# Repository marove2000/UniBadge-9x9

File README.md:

# UniBadge 9x9
A simple badge PCP with 9x9 LEDs. Create symbols, figures, pixel art by just soldering LEDs to the spots you want. No programming needed.

## Bill of Material
| Designator | Package            | Quantity | Designation                    |
| ---------- | ------------------ | -------- | ------------------------------ |
| BT1        | 2-Pin connector    | 1        | Battery-Holder (2xAAA)         |
| C1, C2     | 100nF              | 2        |                                |
| C3         | 0805 SMD capacitor | 1        | variable (see capaictor table) |
| D1-D81     | 0805 SMD LED       | 1-81     | LED red, green, orange, ...    |
| Q1-Q9      | Mosfet             | 9        | 2N7002                         |
| R1, R2     | 0805 SMD resistor  | 2        | 100k                           |
| R3-R11     | 0805 SMD resistor  | 9        | variable (see resistor table)  |
| SW1        | SMD switch         | 1        |                                |
| U1         | SOIC-8 NE555       | 1        |                                |
| U2         | SOP-16 CD4017      | 1        |                                |

### Capacitor-Table for C3
The frequency is determined by the value of C3. Always on: The frequency is so fast, it looks like all (soldered) LEDs are always on.

| Frequency          | Capacitor Value (C3)       |
| ------------------ | -------------------------- |
| slow (~5Hz)        | 1µF                        |
| faster (~50Hz)     | 10nF                       |
| always on (~110Hz) | 4700pF / 4,7nF             |

### Resistor-Table for R3-R11
Resistor values depend on the number of soldered LEDs per row (refer to the table below). Note that you can only choose one LED color per row.

| Number of LEDs | Resistor value for red LEDs | Resistor value for green LEDs (bright!) |
| -------------- | --------------------------- | --------------------------------------- |
| 1              | 56 Ohm                      | 110 Ohm                                 |
| 2              | 27 Ohm                      | 56 Ohm                                  |
| 3              | 18 Ohm                      | 36 Ohm                                  |
| 4              | 15 Ohm                      | 30 Ohm                                  |
| 5              | 11 Ohm                      | 22 Ohm                                  |
| 6              | 9,1 Ohm                     | 18 Ohm                                  |
| 7              | 8,2 Ohm                     | 16 Ohm                                  |
| 8              | 6,8 Ohm                     | 13 Ohm                                  |
| 9              | 6,2 Ohm                     | 12 Ohm                                  |

## Manual
TBD

## Some creations
Some $humans did an amazing job. Here are some awesome examples:

## Copyright and Authorship
- PCB layout: [CC-BY-SA 4.0](https://creativecommons.org/licenses/by-sa/4.0/) - [Thomas Schmid and Timo Schindler](https://www.binary-kitchen.de)
- Manual (TeX): [LPPL](https://www.latex-project.org/lppl.txt) - [Marei Peischl](https://peitex.de)
- Manual (pdf): [CC-BY-SA 4.0](https://creativecommons.org/licenses/by-sa/4.0/) - [Binary Kitchen e.V.](https://www.binary-kitchen.de)

## Acknowledgments
A big thank you goes to Thomas Schmid, Clemens Grünewald and Sandra Schweighart for all the help!

The calculation of the frequency done with https://ohmslawcalculator.com/555-astable-calculator

## Misc: Logo to PCB
The Logos to the PCB are created with an Inkscape plugin

- download and install https://github.com/badgeek/svg2shenzhen
- Inkscape: Extensions -> svg2shenzhen -> Prepare Document
- Choose Layer where to place the logo
- Rename: remove "disabled" from layer-name
- Place logo
- Extensions -> svg2shenshen -> Export Kicad (Kicad-module)
- Copy .kicad_mod in .pretty-folder
- Place as part

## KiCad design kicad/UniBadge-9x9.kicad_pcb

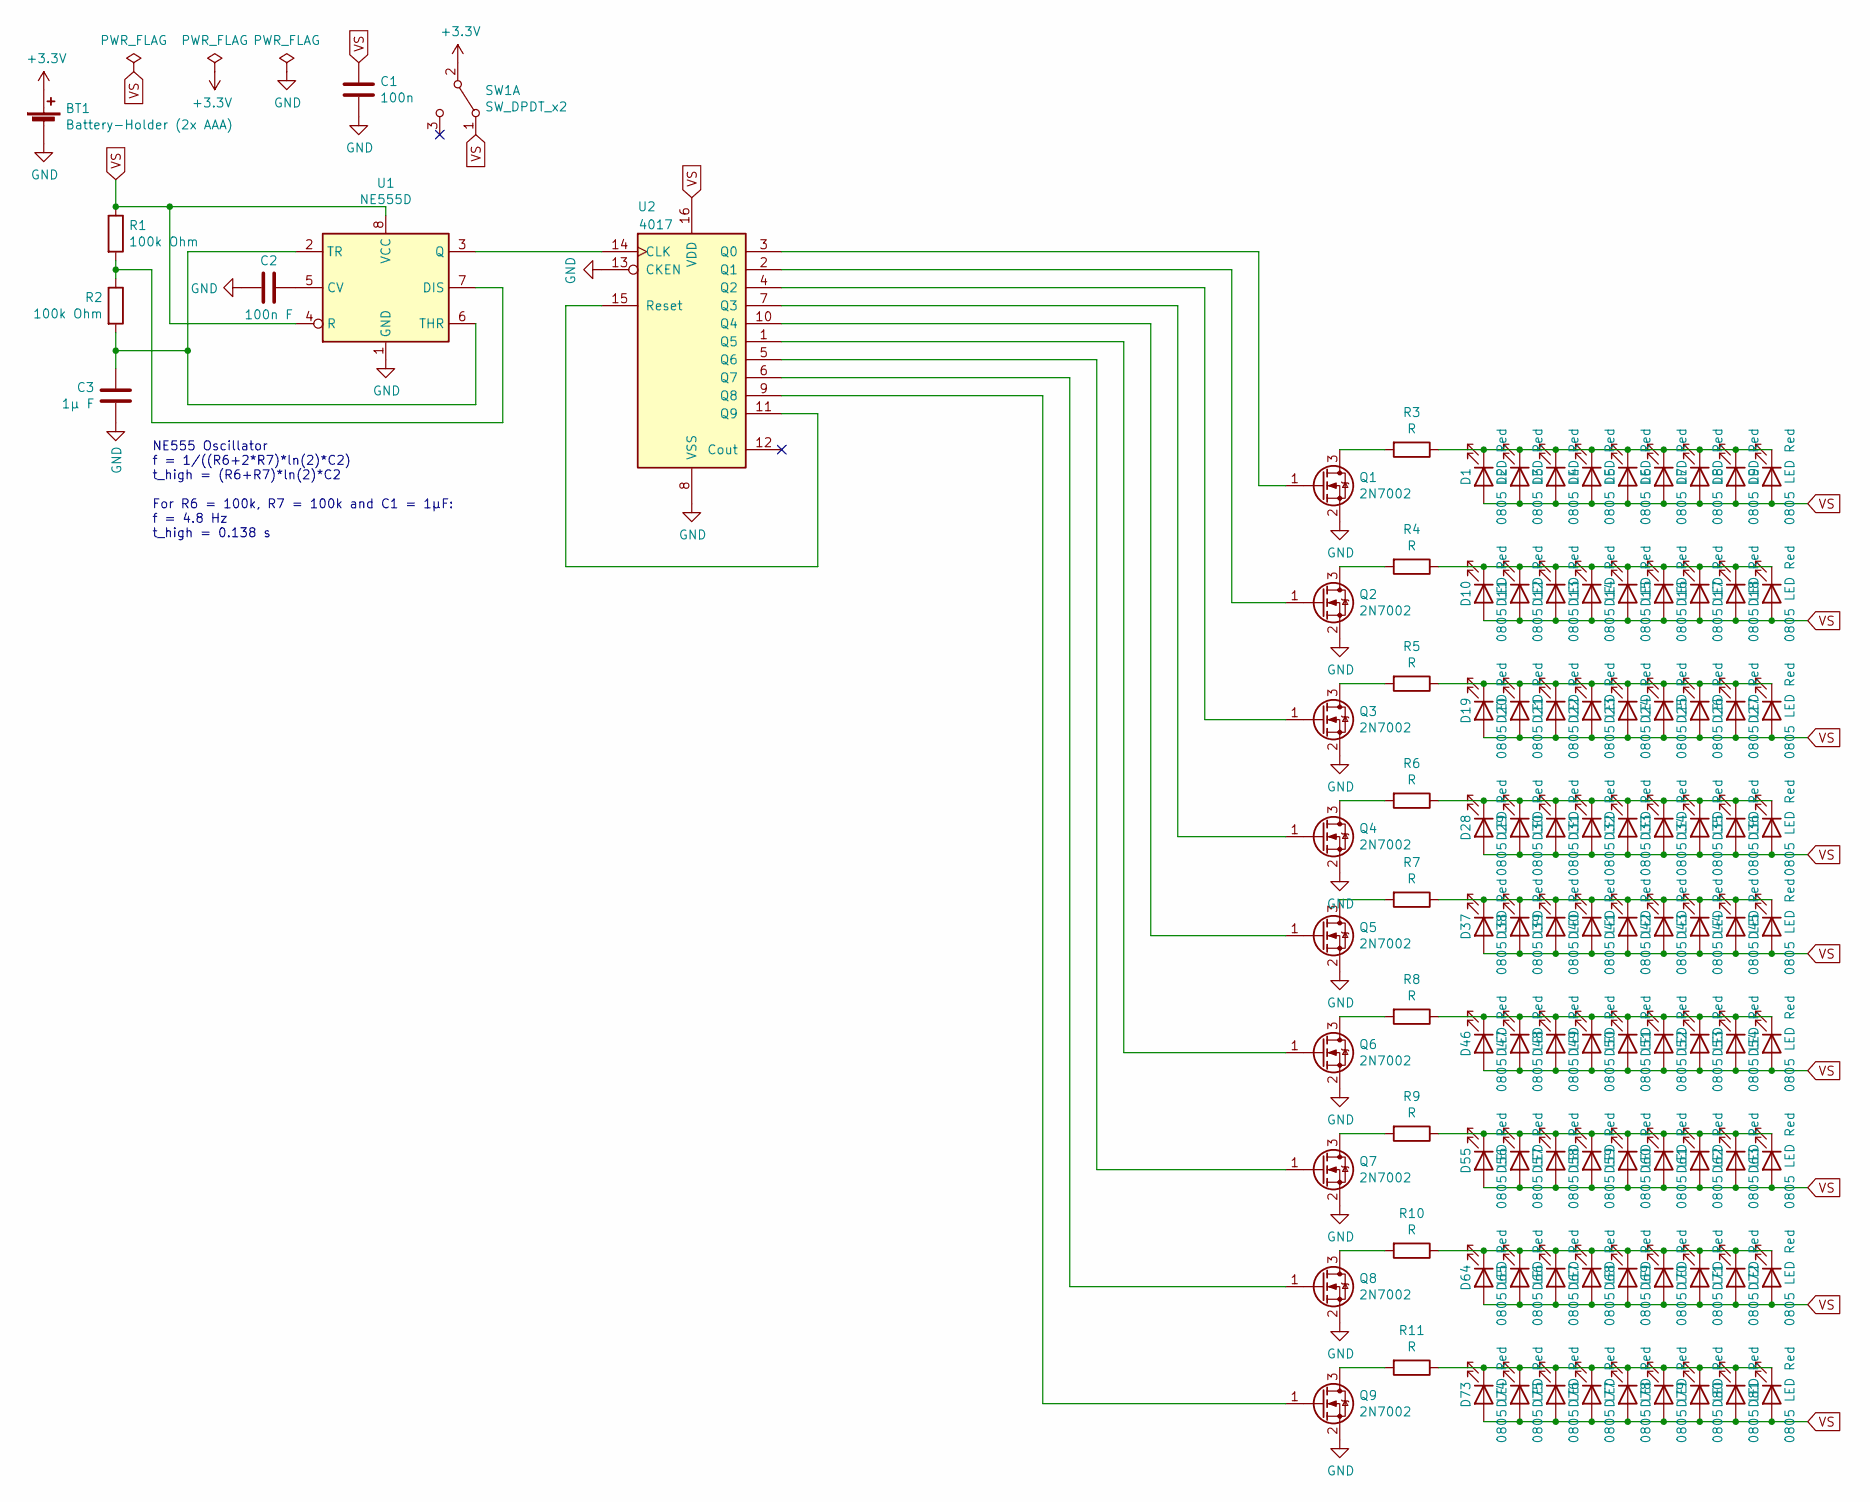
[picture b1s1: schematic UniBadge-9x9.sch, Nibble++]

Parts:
BT1: Battery-Holder (2x AAA); PinHeader_1x02_P2.54mm_Vertical
C1: 100n; C_0805_2012Metric_Pad1.15x1.40mm_HandSolder
C2: 100n F; C_0805_2012Metric_Pad1.15x1.40mm_HandSolder
C3: 1µ F; C_0805_2012Metric_Pad1.15x1.40mm_HandSolder
D1, D2, D3, D4, D5, D6, D7, D8, D9, D10, D11, D12, D13, D14, D15, D16, D17, D18, D19, D20, D21, D22, D23, D24, D25, D26, D27, D28, D29, D30, D31, D32, D33, D34, D35, D36, D37, D38, D39, D40, D41, D42, D43, D44, D45, D46, D47, D48, D49, D50, D51, D52, D53, D54, D55, D56, D57, D58, D59, D60, D61, D62, D63, D64, D65, D66, D67, D68, D69, D70, D71, D72, D73, D74, D75, D76, D77, D78, D79, D80, D81: 0805 LED Red; LED_0805_2012Metric_Pad1.15x1.40mm_HandSolder
Q1, Q2, Q3, Q4, Q5, Q6, Q7, Q8, Q9: 2N7002; SOT-23
R1, R2: 100k Ohm; R_0805_2012Metric_Pad1.15x1.40mm_HandSolder
R3, R4, R5, R6, R7, R8, R9, R10, R11: R; R_0805_2012Metric_Pad1.15x1.40mm_HandSolder
SW1: SW_DPDT_x2; smd_switch_slide
U1: NE555D; SOIC-8_3.9x4.9mm_P1.27mm
U2: 4017; SOP-16_4.4x10.4mm_P1.27mm_simple_drawing

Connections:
+3V3: BT1.1 (+), SW1.2 (B)
GND: BT1.2 (-), C1.1, C2.2, C3.1, Q1.2 (S), Q2.2 (S), Q3.2 (S), Q4.2 (S), Q5.2 (S), Q6.2 (S), Q7.2 (S), Q8.2 (S), Q9.2 (S), U1.1 (GND), U2.8 (VSS), U2.13 (CKEN)
unnamed: C2.1, U1.5 (CV)
unnamed: C3.2, R2.2, U1.2 (TR), U1.6 (THR)
unnamed: D1.1 (K), D2.1 (K), D3.1 (K), D4.1 (K), D5.1 (K), D6.1 (K), D7.1 (K), D8.1 (K), D9.1 (K), R3.1
unnamed: D10.1 (K), D11.1 (K), D12.1 (K), D13.1 (K), D14.1 (K), D15.1 (K), D16.1 (K), D17.1 (K), D18.1 (K), R4.1
unnamed: D19.1 (K), D20.1 (K), D21.1 (K), D22.1 (K), D23.1 (K), D24.1 (K), D25.1 (K), D26.1 (K), D27.1 (K), R5.1
unnamed: D28.1 (K), D29.1 (K), D30.1 (K), D31.1 (K), D32.1 (K), D33.1 (K), D34.1 (K), D35.1 (K), D36.1 (K), R6.1
unnamed: D37.1 (K), D38.1 (K), D39.1 (K), D40.1 (K), D41.1 (K), D42.1 (K), D43.1 (K), D44.1 (K), D45.1 (K), R7.1
unnamed: D46.1 (K), D47.1 (K), D48.1 (K), D49.1 (K), D50.1 (K), D51.1 (K), D52.1 (K), D53.1 (K), D54.1 (K), R8.1
unnamed: D55.1 (K), D56.1 (K), D57.1 (K), D58.1 (K), D59.1 (K), D60.1 (K), D61.1 (K), D62.1 (K), D63.1 (K), R9.1
unnamed: D64.1 (K), D65.1 (K), D66.1 (K), D67.1 (K), D68.1 (K), D69.1 (K), D70.1 (K), D71.1 (K), D72.1 (K), R10.1
unnamed: D73.1 (K), D74.1 (K), D75.1 (K), D76.1 (K), D77.1 (K), D78.1 (K), D79.1 (K), D80.1 (K), D81.1 (K), R11.1
unnamed: Q1.1 (G), U2.3 (Q0)
unnamed: Q1.3 (D), R3.2
unnamed: Q2.1 (G), U2.2 (Q1)
unnamed: Q2.3 (D), R4.2
unnamed: Q3.1 (G), U2.4 (Q2)
unnamed: Q3.3 (D), R5.2
unnamed: Q4.1 (G), U2.7 (Q3)
unnamed: Q4.3 (D), R6.2
unnamed: Q5.1 (G), U2.10 (Q4)
unnamed: Q5.3 (D), R7.2
unnamed: Q6.1 (G), U2.1 (Q5)
unnamed: Q6.3 (D), R8.2
unnamed: Q7.1 (G), U2.5 (Q6)
unnamed: Q7.3 (D), R9.2
unnamed: Q8.1 (G), U2.6 (Q7)
unnamed: Q8.3 (D), R10.2
unnamed: Q9.1 (G), U2.9 (Q8)
unnamed: Q9.3 (D), R11.2
unnamed: R1.2, R2.1, U1.7 (DIS)
unnamed: U1.3 (Q), U2.14 (CLK)
unnamed: U2.11 (Q9), U2.15 (Reset)
VS: C1.2, D1.2 (A), D2.2 (A), D3.2 (A), D4.2 (A), D5.2 (A), D6.2 (A), D7.2 (A), D8.2 (A), D9.2 (A), D10.2 (A), D11.2 (A), D12.2 (A), D13.2 (A), D14.2 (A), D15.2 (A), D16.2 (A), D17.2 (A), D18.2 (A), D19.2 (A), D20.2 (A), D21.2 (A), D22.2 (A), D23.2 (A), D24.2 (A), D25.2 (A), D26.2 (A), D27.2 (A), D28.2 (A), D29.2 (A), D30.2 (A), D31.2 (A), D32.2 (A), D33.2 (A), D34.2 (A), D35.2 (A), D36.2 (A), D37.2 (A), D38.2 (A), D39.2 (A), D40.2 (A), D41.2 (A), D42.2 (A), D43.2 (A), D44.2 (A), D45.2 (A), D46.2 (A), D47.2 (A), D48.2 (A), D49.2 (A), D50.2 (A), D51.2 (A), D52.2 (A), D53.2 (A), D54.2 (A), D55.2 (A), D56.2 (A), D57.2 (A), D58.2 (A), D59.2 (A), D60.2 (A), D61.2 (A), D62.2 (A), D63.2 (A), D64.2 (A), D65.2 (A), D66.2 (A), D67.2 (A), D68.2 (A), D69.2 (A), D70.2 (A), D71.2 (A), D72.2 (A), D73.2 (A), D74.2 (A), D75.2 (A), D76.2 (A), D77.2 (A), D78.2 (A), D79.2 (A), D80.2 (A), D81.2 (A), R1.1, SW1.1 (A), U1.4 (R), U1.8 (VCC), U2.16 (VDD)

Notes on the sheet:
NE555 Oscillator f = 1/((R6+2*R7)*ln(2)*C2) t_high = (R6+R7)*ln(2)*C2 For R6 = 100k, R7 = 100k and C1 = 1µF: f = 4.8 Hz t_high = 0.138 s

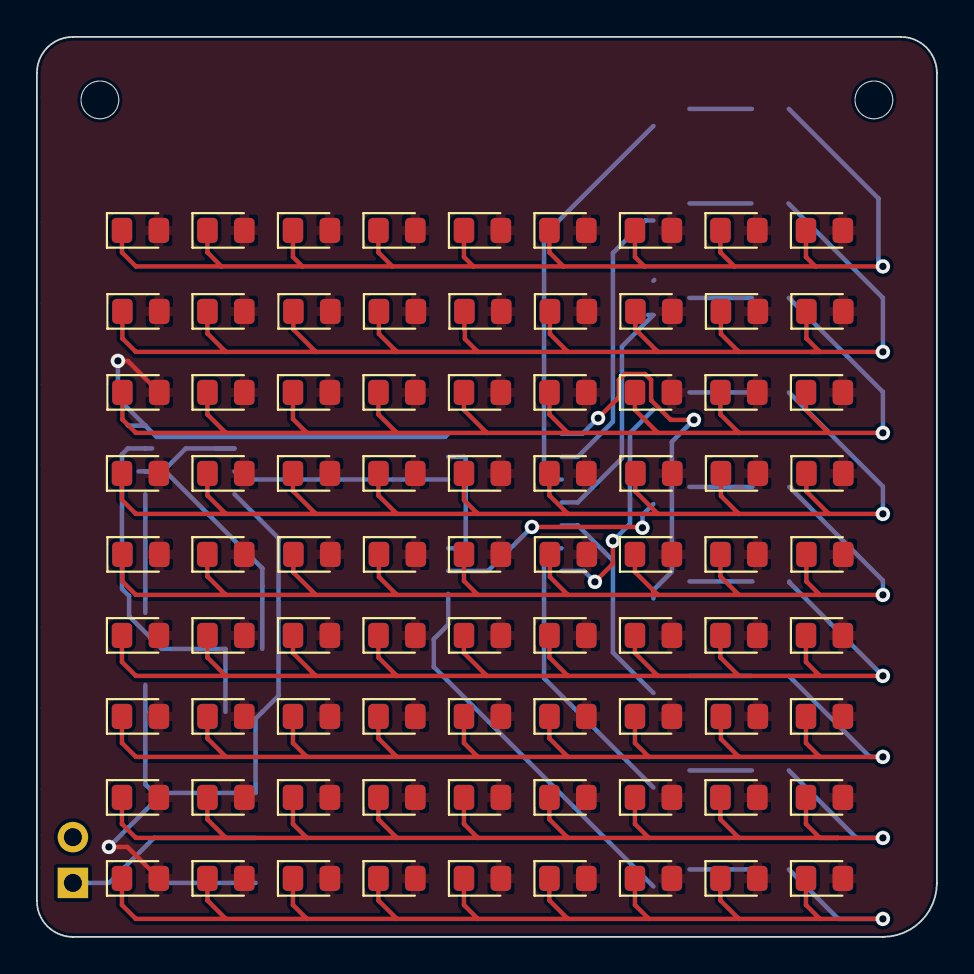
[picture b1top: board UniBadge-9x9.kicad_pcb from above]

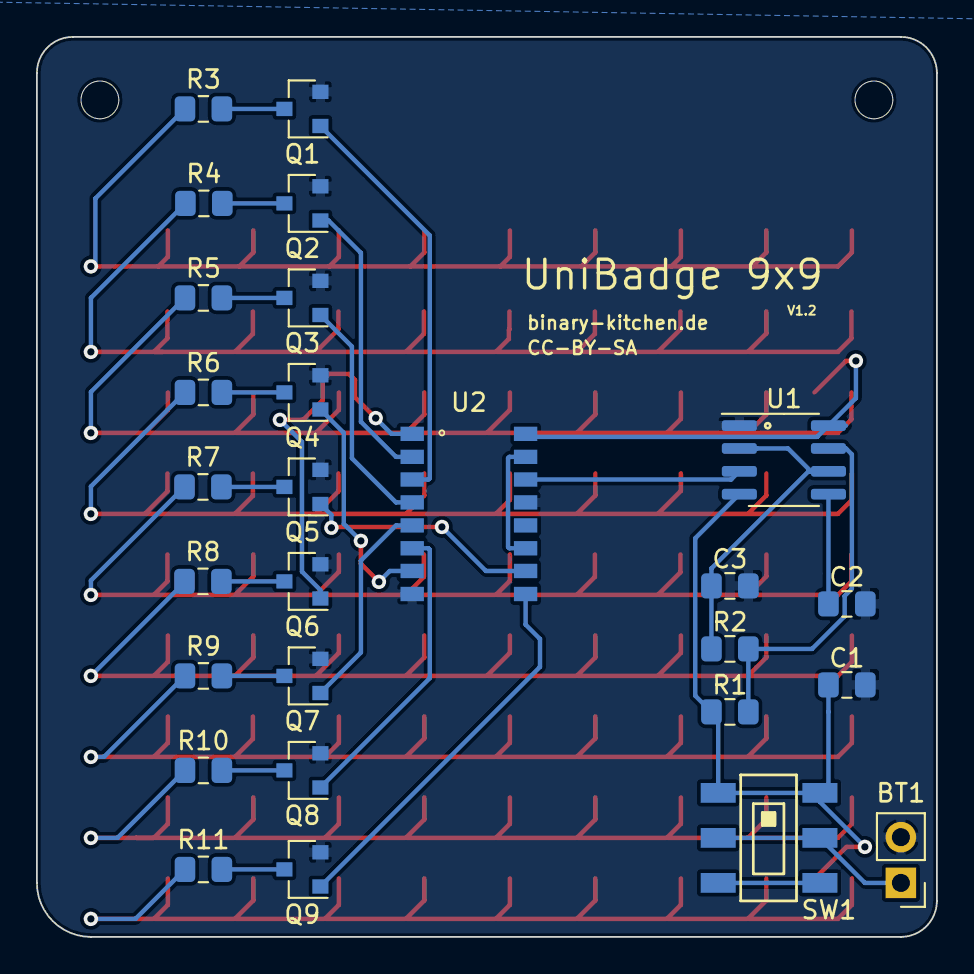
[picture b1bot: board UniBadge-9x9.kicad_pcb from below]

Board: 2 copper layers, 50.0 x 50.0 mm, 110 parts (27 on the bottom side), 35 nets.

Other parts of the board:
Ref**: Val**; vvoidcamp-logo
Ref**#2: Val**; vvoidcamp-schriftzug

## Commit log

2020-07-25 inital commit
2020-08-05 changed layout to simpler 9x9 leds
2020-08-19 added new gerber files
2020-08-19 added some more info
2020-08-19 added detailed readme
2020-08-19 fixed typo
2020-08-19 fixed some minor bugs
2020-08-19 generated new gerberfile
2020-08-19 finished layout
2020-08-19 renamed unibatch to unibadge
2020-08-19 added licence file
2020-08-19 deleted gerber.zip
2020-08-19 renamed unibatch to unibadge ... germans...
2020-08-19 added some misc files
2020-08-19 README: There is no thing like PCB-layout
    Must be a new invention that I missed.
2020-08-19 LICENSE: ... don't call it a Schnitzel
    It's called LICENSE and not LICENCE.
2020-08-19 README: make is understandabler
2020-08-19 README: There is not thing like frequency-calculation
2020-08-19 README: yet another typo fix
    Siss masst be spelled korrektli!
2020-08-19 README: fix typo "pxiel" -> pixel
    This rectifies the misspelled "pxiel". Simply replace it with the
    correctly spelled "pixel" ([pˈɪksə͡l], IPA phonetic alphabet).
    As a drive-by catch, remove the trailing whitespace of the affected
    line.
    No functional change.
2020-08-19 README: Again, LOWERCASE, Lowercase, lowercase
2020-08-19 README: use correct capitalisation for "badge"
    According to the Oxford manual of Style (ref. [1], p. 4), "do NOT use a
    capital letter unless it is absolutely required".
    The use of Badge is a absolutely obvious violation of this rule. Fix
    this major issue by using a 'b' instead of a 'B' (ASCII offset 20
    (0x14)).
    This fix is in alignment with the Chicago manual of Style [2] Part II,
2020-08-19 LICENSE: remove -x flag
    No need to make the LICENSE file executable, unless we want to use it as
    a backdoor.
2020-08-19 README: There is no thing like LED-Color
    use LED color instead.
2020-08-19 README: tables: fix capitalisation
2020-08-19 README: fix spelling
    old swedish man.
2020-08-19 README: s/carefull/careful/
    According to https://dict.leo.org/englisch-deutsch/careful this should
    only be written with a single 'l'.
2020-08-19 README: use active construction instead of making use of gerunds
    According to Lyn Dupré, "BUGS in Writing: A Guide to Debugging Your
    Prose", active constructions should be the construct of choice.
    Additionaly, let's spend a second 'o' for choose.
2020-08-20 added gitignore
2020-08-20 added new net-list
2020-08-20 fixed clock-enable at cd4017
2020-08-20 generated new gerber-files
2020-08-25 Updated resistor values for LEDs
2020-09-02 added some creations
2020-09-02 added some more examples
